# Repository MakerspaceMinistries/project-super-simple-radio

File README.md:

# Version Name #

`v<version>-<antenna type><audio output><station select><configuration location>`

- version: version number - corresponds with firmware
- antennta type: 
    O) onboard ESP32 antenna
    U) external antenna (following Espressif's convention)
- audio output:
    S) speakers
    L) line out
- station select:
    S) single station (no selector)
    M) multi station
- configuration location
    H) hardcoded
    R) remote

# Overview #

## Connecting to the radio for programming and debugging ##
There are two ways to connect: 

1. USB->Serial, using pads on the PCB
2. On board USB, via micro USB port on the PCB

USB->Serial appears to be the best for troubleshooting and development, as it is more verbose. To save money, this is achieved by connecting an extermal USB->Serial cable to pads on the PCB. This way one set of USB->Serial hardware can be used for multiple devices.

The ESP32 S3's onboard OTG USB does not appear to recieve the ESP32's debug messages, so it's not a solution for troubleshooting and development. However, it does provide a cheap way to make firmware updates more convenient.

### Linux ###

Create a udev rule so that it is not necessary to set permissions with each connection, by creating this file `/etc/udev/rules.d/99-esp32s3.rules` and adding this lines:

```
ATTRS{idVendor}=="303a", ATTRS{idProduct}=="1001", MODE="0666", ENV{ID_MM_DEVICE_IGNORE}="1", ENV{ID_MM_PORT_IGNORE}="1"
ATTRS{idVendor}=="0403", ATTRS{idProduct}=="6001", MODE="0666", ENV{ID_MM_DEVICE_IGNORE}="1", ENV{ID_MM_PORT_IGNORE}="1"
```

Then restart udev:

`sudo systemctl restart udev`

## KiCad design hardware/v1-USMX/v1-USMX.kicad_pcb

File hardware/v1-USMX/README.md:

# Parts & Datasheets #

## ESP32-S3-WROOM-1U-N16R8 ##

Purchase: https://www.mouser.com/ProductDetail/356-ESP32S3WM1UN16R8

### Datasheets And Other Resources ###

Many of the circuits required for the radio are also found on the ESP32 S3 Dev Kits & ESP32 S3 Korvo Dev Board, . The schematics are helpful for reference.

- Espressif datasheet for the ESP32-S3-WROOM-1/U module https://www.espressif.com/sites/default/files/documentation/esp32-s3-wroom-1_wroom-1u_datasheet_en.pdf
    - Page 25: example schematics
    - Page 12: strapping pins
    - Page 10-11: module pinout
- Espressif ESP32 hardware design guidelines https://www.espressif.com/sites/default/files/documentation/esp32_hardware_design_guidelines_en.pdf
- ESP32 S3 Dev Kit Schematics https://dl.espressif.com/dl/schematics/SCH_ESP32-S3-DevKitC-1_V1.1_20220413.pdf
- ESP32 S3 Dev Kit PCB Layout: https://dl.espressif.com/dl/schematics/PCB_ESP32-S3-DevKitC-1_V1.1_20220429.pdf
- Other Dev Kit resources: https://docs.espressif.com/projects/esp-idf/en/latest/esp32s3/hw-reference/esp32s3/user-guide-devkitc-1.html#related-documents
- ESP32 S3 Korvo (an audio dev board from Espressif): https://docs.espressif.com/projects/esp-adf/en/latest/design-guide/dev-boards/user-guide-esp32-s3-korvo-2.html

### Footprints/Schematics ###

Download or clone the Espressif Library repo: https://github.com/espressif/kicad-libraries

Install the symbols, footprints, and 3D models:

1. `Preferences` -> `Manage Symbol Libraries` and add a library and specify the `libraries/Espressif.kicad_sym` in the repo as the Library Path.
2. `Preferences` -> `Manage Footprint Libraries` and add a library and specify the `footprints\Espressif.pretty` in the repo as the Library Path.
3. `Preferences` -> `Configure Paths`
    * Create a new variable:
        * Name: `ESPRESSIF_3DMODELS`
        * Path: `<path to the folder kicad-libraries/3d>`

## MAX98357AETE+T - DAC & Amplifier ##

Datasheet: https://www.mouser.com/datasheet/2/256/MAX98357A-MAX98357B-271244.pdf  
Purchase: https://www.mouser.com/ProductDetail/Maxim-Integrated/MAX98357AETE%2bT?qs=AAveGqk956HhNpoJjF5x2g%3D%3D
Footprint/Schematic: https://componentsearchengine.com/part-view/MAX98357AETE%2BT/Maxim%20Integrated 

## AZ1084CD-3.3TRG1 - Voltage Regulator (3.3v) ##

Datasheet: https://www.diodes.com/assets/Datasheets/AZ1084C.pdf  
Purchase: https://www.mouser.com/ProductDetail/621-AZ1084CD-3.3TRG1

This footprint and schematic are for the same line as the AZ1084CD-3.3TRG1

https://componentsearchengine.com/part-view/AZ1084CD-ADJTRG1/Diodes%20Inc.

## P110KH1-0F15BR10Kb - Volume Potentiomoter ##

Datasheet: https://www.mouser.com/datasheet/2/414/TTRB_S_A0010315417_1-2565498.pdf  
Purchase: https://www.mouser.com/ProductDetail/BI-Technologies-TT-Electronics/P110KH1-0F15BR10K?qs=%252BUYXD5bnyXryQEHfrY0%252Baw%3D%3D
Footprint/Schematic: https://componentsearchengine.com/part-view/P110KH1-0F15BR10K/BI%20Technologies

## PTA3043-2015DPB104 - Station Potentiometer ##

Datasheet: https://www.mouser.com/datasheet/2/54/pta-778345.pdf  
Purchase:  https://www.mouser.com/ProductDetail/Bourns/PTA3043-2015DPB104?qs=zRGnDeWDVj0fVt3rAxibYA%3D%3D
Footprint/Schematic: https://componentsearchengine.com/part-view/PTA3043-2015DPB104/Bourns

## CLMVC-FKC-CGJJM569aBB7a343 - RGB LED ##

Datasheet: https://www.mouser.com/datasheet/2/723/1273_CLMVC_FKA-2326704.pdf  
Purchase: https://www.mouser.com/ProductDetail/Cree-LED/CLMVC-FKC-CGJJM569aBB7a343?qs=1mbolxNpo8epafm4p5CBBQ%3D%3D

The footprint and schematic for the CLMVC-FKC-CGJJM569aBB7a343 wasn't available, however, this LED has the same packing and pinout.

https://componentsearchengine.com/part-view/CLMVC-FKA-CL1D1L71BB7C3C3/Wolfspeed

## GG060305100N2P - ESD Suppressor ##

***IMPORTANT*** & ***TODO***  
*The selection of this ESD suppressor may be wrong. The ESP32 S3 Dev Kit and the ESP32 S3 Korvo both use the LESD5D5.0CT1G, which is no longer available. The GG060305100N2P appears to have similar specs, but this should be verified by someone with who is more knowledgeable*

Datasheet: https://www.mouser.com/datasheet/2/40/AVX_GiGuard-2401264.pdf  
Purchase: https://www.mouser.com/ProductDetail/KYOCERA-AVX/GG060305100N2P?qs=QNEnbhJQKvZ38qL0Ea5hYg%3D%3D  
Package/Case: 0603 (1610 metric)
Footprint/Schematic: https://componentsearchengine.com/part-view/GG060305100N2P/Kyocera%20AVX

## Resistors ##

Package/case: 1206/3216 (in/mm)
Footprint: Built-in 1206 footprint

270 ohm
- CR1206-FX-2700ELF
- https://www.mouser.com/ProductDetail/Bourns/CR1206-FX-2700ELF?qs=UUWDWenVDLhTOwaXSP1D9Q%3D%3D

10k ohm
- CR1206-FX-1002ELF
- https://www.mouser.com/ProductDetail/Bourns/CR1206-FX-1002ELF?qs=3wWX5hyYeeQyTehaX7pP%252BA%3D%3D

220k ohm
- CR1206-FX-2203ELF
- https://www.mouser.com/ProductDetail/Bourns/CR1206-FX-2203ELF?qs=UUWDWenVDLhp0KvMMxHtXw%3D%3D

## 10uF Ceramic Capacitor ##

Package/case: 0805/2012 (in/mm)
Footprint: Built-in 0805 footprint

10uF 16v
- Model: CL21B106KAYQNNE
- Purchase: https://www.mouser.com/ProductDetail/187-CL21A106KOQNNNG

0.1uF 25v
- Model: CL21B104KACNNNC
- Purchase: https://www.mouser.com/ProductDetail/Samsung-Electro-Mechanics/CL21B104KACNNNC?qs=yOVawPpwOwnhB47kNbieFw%3D%3D

## Tactile Switches - Reset and Reset & Program ##

Datasheet: https://www.mouser.com/datasheet/2/240/pts526-3050698.pdf
Purchase: https://www.mouser.com/ProductDetail/CK/PTS526-SM08-SMTR2-LFS?qs=UXgszm6BlbFgRZzlfGAMFg%3D%3D
Footprint/Shematic: https://componentsearchengine.com/part-view/PTS526%20SM08%20SMTR2%20LFS/C%20%26%20K%20COMPONENTS

## USB Micro ##

Datasheet: https://cdn.amphenol-cs.com/media/wysiwyg/files/documentation/datasheet/inputoutput/io_usb_micro.pdf
Drawing: https://www.amphenol-cs.com/media/wysiwyg/files/drawing/10118192.pdf  
Purchase: https://www.mouser.com/ProductDetail/Amphenol-FCI/10118192-0002LF?qs=KVgMXE4aH4nIkuWlMxQzog%3D%3D
Footprint/Schematic: https://componentsearchengine.com/part-view/10118192-0002LF/Amphenol%20Communication%20Solutions 

# Other Hardware Options #

These are options that were not used, but may be useful for future designs.

## 90 Tactile Switch - Reset ##
https://www.mouser.com/ProductDetail/E-Switch/TL3336AF160Q?qs=iLbezkQI%252Bshf0NMs3%252BGhxA%3D%3D

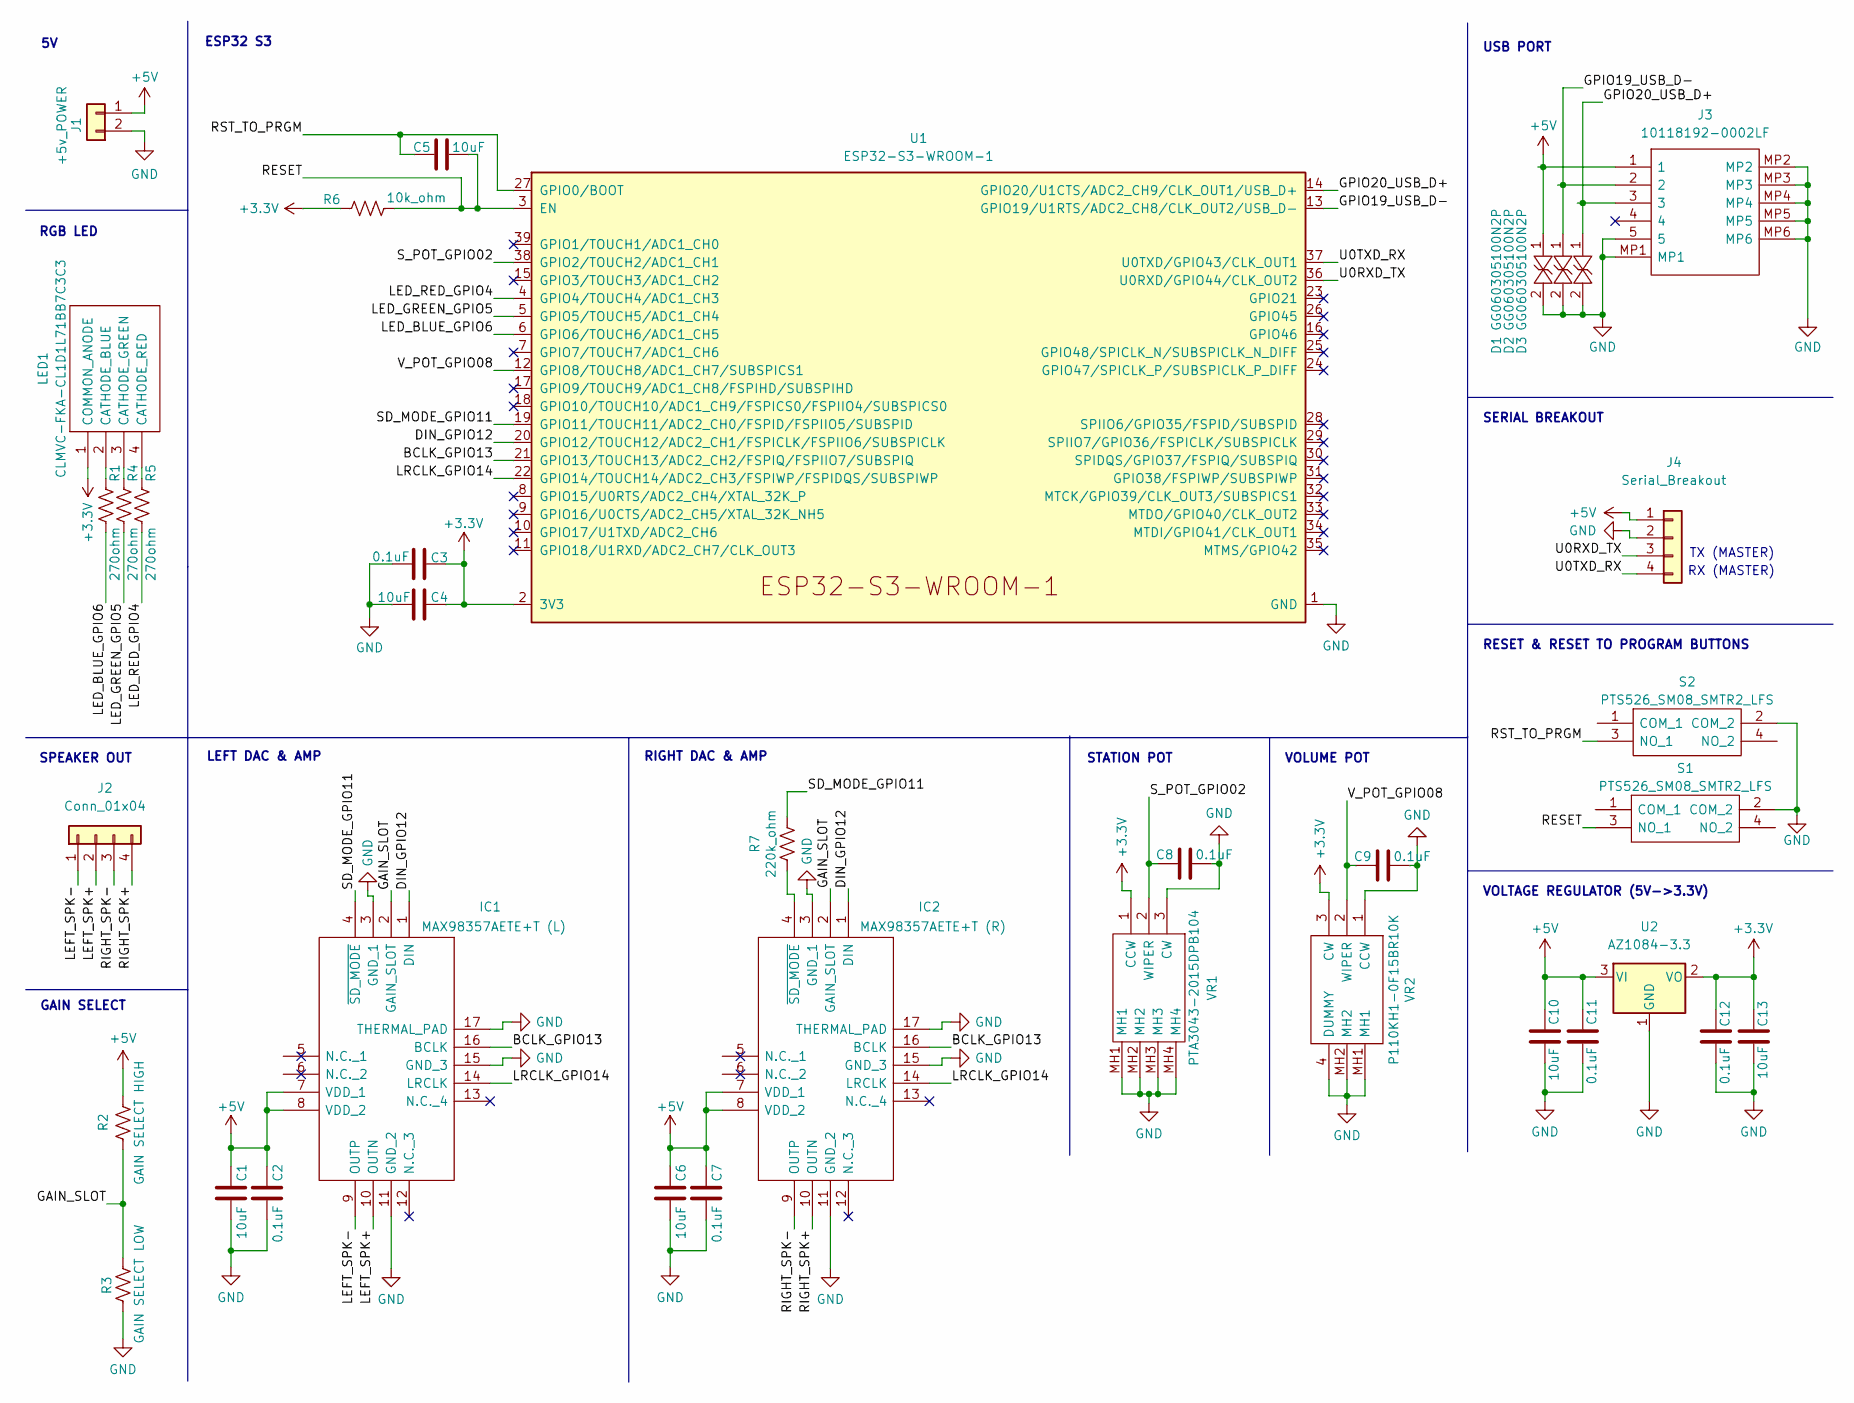
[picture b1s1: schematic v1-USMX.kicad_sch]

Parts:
C1, C4, C5, C6, C10, C13: 10uF; C_0805_2012Metric
C2, C3, C7, C8, C9, C11, C12: 0.1uF; C_0805_2012Metric
D1, D2, D3: GG060305100N2P; DIONC1608X70N; Manufacturer_Part_Number GG060305100N2P; Mouser Part Number 581-GG060305100N2P
IC1: MAX98357AETE+T (L); QFN50P300X300X80-17N; Manufacturer_Part_Number MAX98357AETE+T; Mouser Part Number 700-MAX98357AETE+T
IC2: MAX98357AETE+T (R); QFN50P300X300X80-17N; Manufacturer_Part_Number MAX98357AETE+T; Mouser Part Number 700-MAX98357AETE+T
J1: +5v_POWER; CUSTOM_5V_SOLDER_PADS
J2: Conn_01x04; JST_XH_B4B-XH-A_1x04_P2.50mm_Vertical
J3: 10118192-0002LF; 101181920002LF; Manufacturer_Part_Number 10118192-0002LF; Mouser Part Number 649-10118192-0002LF
J4: Serial_Breakout; PinHeader_2x02_P2.54mm_Vertical
LED1: CLMVC-FKA-CL1D1L71BB7C3C3; CLMVCFKACL1D1L71BB7C3C3; Manufacturer_Part_Number CLMVC-FKA-CL1D1L71BB7C3C3; Mouser Part Number 941-CLMVCFKACL1D1L71
R1, R4, R5: 270ohm; R_1206_3216Metric
R2: GAIN SELECT HIGH; R_1206_3216Metric
R3: GAIN SELECT LOW; R_1206_3216Metric
R6: 10k_ohm; R_1206_3216Metric
R7: 220k_ohm; R_1206_3216Metric
S1, S2: PTS526_SM08_SMTR2_LFS; PTS526SM08SMTR2LFS; Manufacturer_Part_Number PTS526 SM08 SMTR2 LFS; Mouser Part Number 611-PTS526SM08SMTR2L
U1: ESP32-S3-WROOM-1; ESP32-S3-WROOM-1U
U2: AZ1084-3.3; TO-252-2
VR1: PTA3043-2015DPB104; PTA30432015DPB104; Manufacturer_Part_Number PTA3043-2015DPB104; Mouser Part Number 652-PTA30432015B104
VR2: P110KH1-0F15BR10K; P110KH10F15BR10K; Manufacturer_Part_Number P110KH1-0F15BR10K; Mouser Part Number 858-P110KH10F15BR10K

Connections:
+3.3V: C3.1, C4.1, C12.1, C13.1, LED1.1 (COMMON_ANODE), R6.1, U1.2 (3V3), U2.2 (VO), VR1.1 (CCW), VR2.3 (CW)
+5V: C1.1, C2.1, C6.1, C7.1, C10.1, C11.1, D1.1, IC1.7 (VDD_1), IC1.8 (VDD_2), IC2.7 (VDD_1), IC2.8 (VDD_2), J1.1, J3.1, J4.1, R2.1, U2.3 (VI)
/BCLK_GPIO13: IC1.16 (BCLK), IC2.16 (BCLK), U1.21 (GPIO13/TOUCH13/ADC2_CH2/FSPIQ/FSPIIO7/S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)
/DIN_GPIO12: IC1.1 (DIN), IC2.1 (DIN), U1.20 (GPIO12/TOUCH12/ADC2_CH1/FSPICLK/FSPIIO6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)
/GAIN_SLOT: IC1.2 (GAIN_SLOT), IC2.2 (GAIN_SLOT), R2.2, R3.2
/GPIO19_USB_D-: D2.1, J3.2, U1.13 (GPIO19/U1RTS/ADC2_CH8/CLK_OUT2/USB_D-)
/GPIO20_USB_D+: D3.1, J3.3, U1.14 (GPIO20/U1CTS/ADC2_CH9/CLK_OUT1/USB_D+)
/LED_BLUE_GPIO6: R1.1, U1.6 (GPIO6/TOUCH6/ADC1_CH5)
/LED_GREEN_GPIO5: R4.1, U1.5 (GPIO5/TOUCH5/ADC1_CH4)
/LED_RED_GPIO4: R5.1, U1.4 (GPIO4/TOUCH4/ADC1_CH3)
/LEFT_SPK+: IC1.10 (OUTN), J2.2
/LEFT_SPK-: IC1.9 (OUTP), J2.1
/LRCLK_GPIO14: IC1.14 (LRCLK), IC2.14 (LRCLK), U1.22 (GPIO14/TOUCH14/ADC2_CH3/FSPIWP/FSPIDQS/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)
/RESET: C5.1, R6.2, S1.3 (NO_1), U1.3 (EN)
/RIGHT_SPK+: IC2.10 (OUTN), J2.4
/RIGHT_SPK-: IC2.9 (OUTP), J2.3
/RST_TO_PRGM: C5.2, S2.3 (NO_1), U1.27 (GPIO0/BOOT)
/SD_MODE_GPIO11: IC1.4 (~SD_MODE), R7.2, U1.19 (GPIO11/TOUCH11/ADC2_CH0/FSPID/FSPIIO5/S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)
/S_POT_GPIO02: C8.1, U1.38 (GPIO2/TOUCH2/ADC1_CH1), VR1.2 (WIPER)
/U0RXD_TX: J4.3, U1.36 (U0RXD/GPIO44/CLK_OUT2)
/U0TXD_RX: J4.4, U1.37 (U0TXD/GPIO43/CLK_OUT1)
/V_POT_GPIO08: C9.1, U1.12 (GPIO8/TOUCH8/ADC1_CH7/SUBSPICS1), VR2.2 (WIPER)
GND: C1.2, C2.2, C3.2, C4.2, C6.2, C7.2, C8.2, C9.2, C10.2, C11.2, C12.2, C13.2, D1.2, D2.2, D3.2, IC1.3 (GND_1), IC1.11 (GND_2), IC1.15 (GND_3), IC1.17 (THERMAL_PAD), IC2.3 (GND_1), IC2.11 (GND_2), IC2.15 (GND_3), IC2.17 (THERMAL_PAD), J1.2, J3.5, J3.MP1, J3.MP2, J3.MP3, J3.MP4, J3.MP5, J3.MP6, J4.2, R3.1, S1.2 (COM_2), S2.2 (COM_2), U1.1 (GND), U1.40 (GND), U1.41 (GND), U2.1 (GND), VR1.3 (CW), VR1.MH1, VR1.MH2, VR1.MH3, VR1.MH4, VR2.1 (CCW), VR2.4 (DUMMY), VR2.MH1, VR2.MH2
unnamed: IC2.4 (~SD_MODE), R7.1
unnamed: LED1.2 (CATHODE_BLUE), R1.2
unnamed: LED1.3 (CATHODE_GREEN), R4.2
unnamed: LED1.4 (CATHODE_RED), R5.2

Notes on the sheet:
RESET & RESET TO PROGRAM BUTTONS
RGB LED
VOLUME POT
LEFT DAC & AMP
STATION POT
SPEAKER OUT
RIGHT DAC & AMP
ESP32 S3
SERIAL BREAKOUT
USB PORT
GAIN SELECT
VOLTAGE REGULATOR (5V->3.3V)
RX (MASTER)
TX (MASTER)

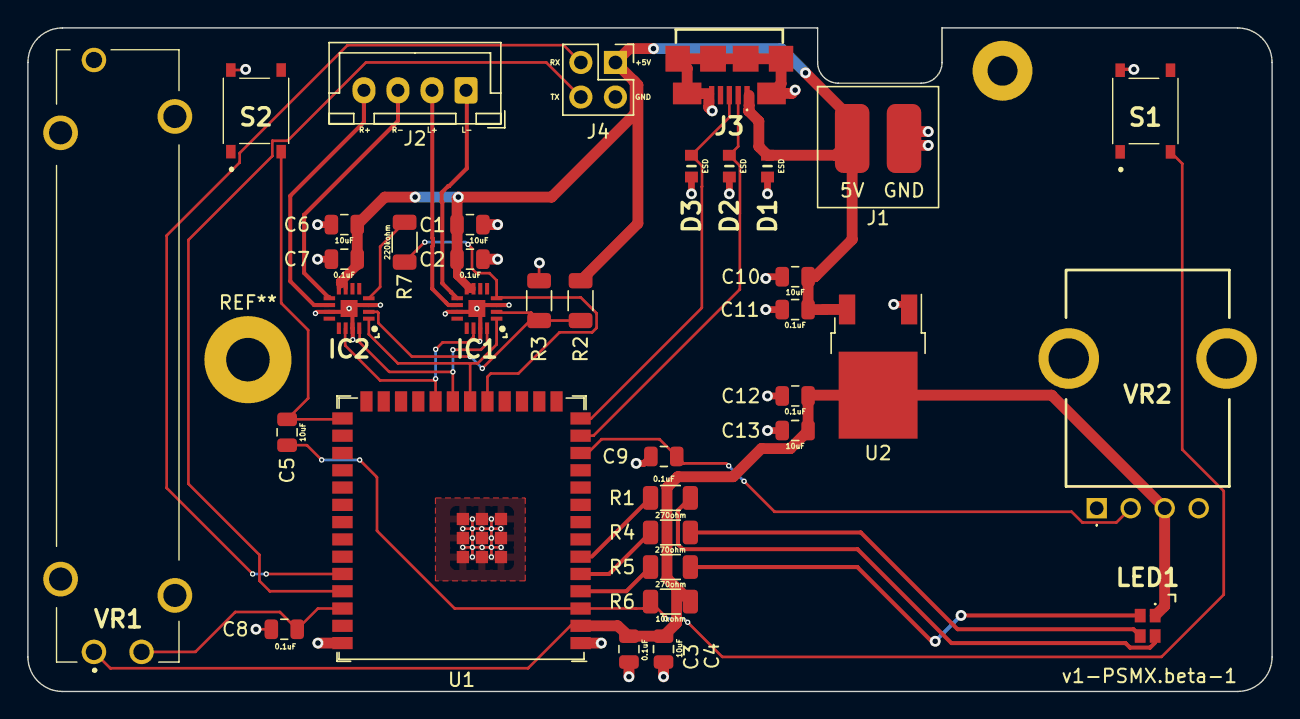
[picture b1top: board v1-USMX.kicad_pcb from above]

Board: 2 copper layers, 91.4 x 48.8 mm, 36 parts (0 on the bottom side), 27 nets.

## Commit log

2022-11-13 init dir structure
2022-11-13 added git ignore
2022-11-13 init work on hardware
2022-11-20 added information to the readmes
2022-11-22 added more information to readmes
2022-11-22 misc
2022-11-25 init work on the firmware readme
2022-11-25 more updates to firmware readme
2022-11-25 Init work on a schematic
2022-11-25 Updated readme for hardware
2022-11-25 add part to parts list
2022-11-26 Init work on hardware schematic
2022-11-28 Updated Readmes
2022-11-28 Init work on schematic
2022-11-28 Improvements to schematic
2022-11-29 Added ESD protection to USB connection
2022-12-06 Completed Init work on schematic
2022-12-11 init work on pcb
2022-12-14 all routed, but needs organized
2022-12-14 Cleaned up pcb
2022-12-15 added silk screen labels for resistor and diode size
2022-12-15 added version number
2022-12-15 Added some more labels
2022-12-15 msic
2022-12-16 Updated track widths to work with 1oz
2022-12-16 added screw hole, misc improvements
2022-12-17 organization
2023-01-08 passes all DRC
2023-01-08 Created Gerbers And Drill
2023-01-15 init work on firmware. added ability to set/retrieve config via preferences. configs in the form of JSON can be sent via serial
2023-01-15 specified the station list refers to remote
2023-01-16 Moved from const char* for settings to String, which is easier for working with preferences.
2023-01-16 refactoring
2023-01-17 init work on WifiManager
2023-01-17 Added LED statuses, including a blinking - giving 8 possible states.
2023-01-17 Set up a way to measure loops per seconds - debugLPS.
2023-01-17 Created an interval for analog reads, which don't need to be updated every loop and are long.
2023-01-17 misc refactoring
2023-01-21 Moved LED Status into its own object & added items to the todo list.
2023-01-21 PCB is passing tests, locked footprints and outline in place.
2023-01-21 Increased the size of some silk screen
2023-01-21 Added ground plane to top, vias at extremeties
2023-01-21 Added LED status to be used during startup. Added wifi connection check
2023-01-21 goes with previous commit
2023-01-21 Added object to read the current channel index from the channel pot
2023-01-22 Init work on a radio object for controlling the radio.
2023-02-04 Refactored radio/channelpot into its own object
2023-02-04 maxStationCount is now hard coded, and not stored in preferences
2023-02-11 Init work on api for the config server
2023-02-13 Init work on api
2023-02-15 documentation init
2023-02-15 updated image name
2023-02-15 init helm chart
2023-02-15 Added a helm chart for the api server, fixed bug where column that didn't exist was selected
2023-02-17 reworked dockerfile so that requirements aren't rebuilt every time the app is changed
2023-02-17 refactored the device interface to a GET, moved the radioID to the end of the URL, to make it easier to work with, moved from array of stations to key/value
2023-02-18 updated value to camelCase so it matches the usage in the firmware.
2023-02-18 update readme with info about psram
2023-07-03 Radio now can optionally get config from a remote server.
2023-07-07 Moved large chunk into a loop inside the radio object, with more to go.
2023-07-08 moved more of the code to the radio object.
2023-07-08 added some comments
2023-07-08 Fixed bug in stream loss detection
2023-07-08 refactored code into Radio.h
2023-07-09 Moved the channels array to an array of pointers instead of a new array
2023-07-13 Major refactor to add status codes to drive the LEDs, and general refactoring
2023-07-13 Fixed bug where LED Statuses were cleared in the wrong direction, improved name
2023-08-03 added example of setting a mac
2023-09-25 Major Refactor
2023-09-25 Serial now begins at init, so that the config can be changed at any time
2023-09-25 Debug mode can now be turned on with serial
2023-09-25 Refactored how status codes are set, allowing them to also clear codes.
2023-09-25 Added a delay before reconnecting to WiFi. Reconnecting is not blocking, so it looped from reconnecting to disconnecting
2023-09-25 The streamIsAdvancing() is not working and now just returns true
2023-09-25 Radio now reconnects if it gets a 404, after a 5 second delay
2023-09-26 Broke up example of serial config into two parts since it won't send otherwise
2023-09-26 removed clash declaration of a global var
2023-09-26 The json doc was much larger than needed
2023-09-26 Reworked how some strings are sent to serial
2023-09-26 Fixed the LED status for when it can't connect to wifi so that it blinks
2023-09-26 Added todo list
2023-09-27 Fixed bug where the UNABLE_TO_CONNECT_TO_WIFI_WM_ACTIVE status wasn't cleared after a good connection
2023-09-27 The response from wifiManager->autoConnect("Radio Setup"); is never false (in a practical way) so the if block was removed and replaced with a loop so that serial input can be handled when wifi manag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
2023-09-27 the esp can now be restarted via serial
2023-09-27 Fix bug where LED reset was used incorrectly, finished testing
2023-09-27 Not customizing setup page at this time. The update function may become useful for programming later on, the other buttons can be explained in a video
2023-09-28 Refactored the loop & added detection for buffering,
2023-10-08 Completely rewrote the LEDStatus object, simplifying it. It is not implemented
2023-10-08 LEDStatus config is now passed at init, not instantiation.
2023-10-08 Changed to work with new LEDStatus object
2023-10-15 style changes, moving to more consistent var names
2023-10-15 Refactored variable names, other style
2023-10-15 Refactored LED Status to have codes for when the LEDs are off, instead of a single code (-1)
2023-10-15 An interval can be set to retrieve the configuration while the radio is idle
2024-01-01 init work on a software for programming radios
2024-01-16 added a better test-radio id
2024-01-17 Added freecad files and stl files for knobs
2024-01-17 Moved info from code to READMEs, and continued work on the serial programmer.
2024-01-17 work on the qr code generator
2024-01-17 added todo
2024-01-18 re-organized and added function from stackoverflow that finds serial ports
2024-01-18 Moved files around
2024-01-18 If the request to the settings server throws an error, then don't update the local config.
2024-01-18 misc doc
2024-01-21 Removed unused screw holes, corrected shape of pads
2024-01-21 Moved serial pins to an area that offers easier access with a clamp fixture, even after installation
2024-01-21 Changed pcb version number
2024-01-23 Added fab files for v1.0-USMX-B
2024-01-23 init station config client
2024-01-27 Added vuetify
2024-01-27 Fixed some permissions, other minor bugs
2024-01-27 Added example for secrets file
2024-01-28 Added CORS to the radio api, for dev and use later. The gunicorn.sh file was no longer(?) working, so the process was executed directly
2024-01-28 If a radio is not found, the server returns a 404
2024-02-03 Init work on webclient
2024-02-06 added reqs for the serial programmer
2024-02-06 refactored so that there's only one serial connection, handled serial more stabily
2024-02-17 Removed blocking code, serial is only handled if there is some available.
2024-02-24 updated chart
2024-02-24 added dockerfile for client
2024-02-24 added v1.0.0-beta.3 firmware
2024-02-24 v1.0.0 beta 2 firmware
2024-02-24 worked out some bugs with the helm chart, get it working in prod
2024-03-22 Restart the ESP if wifi_disconnect_timeout_ms is reached
2024-03-22 Fixed syntax, misc, compiled firmware v1.0.0-beta.4
2024-03-22 Updated version number, fixed bug where timeout was in s, not ms
2024-03-27 Added a timeout for reconnecting, changed some timeout numbers, recompiled firmware
2024-09-10 Added a timeout that restarts the esp if it is in WiFi Setup mode for more than 15 minutes.
    This helps restart after a power failure, where the esp boots before a router and the esp would otherwise be stuck in a loop waiting to be configured.
2025-08-12 Added stl files
2025-08-12 added new version of firmware
2025-08-12 Improves serial port communication and handling
    Refines serial port communication by increasing sleep durations
    after writing data and while reading configuration,
    enhancing reliability.
    Adds serial port auto-detection with an exclusion list to
    prevent connection to unwanted ports.
    Improves output by printing the port being used.
2025-08-12 Adds QR code webcam scanner
    Implements a QR code scanner using the webcam.
    It initializes the camera, captures frames, detects QR codes,
    and extracts a UUID from the decoded data. Includes error
    handling and camera auto-detection for improved reliability
    on Linux systems.
2025-11-07 Updates default target device path
    Updates the default target device path to '/dev/ttyACM0'.
    This resolves an issue where the programmer was not correctly
    targeting the serial device, likely due to a typo in the path.
